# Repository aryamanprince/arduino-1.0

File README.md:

Files to be submitted for Zine robotics and research group interview

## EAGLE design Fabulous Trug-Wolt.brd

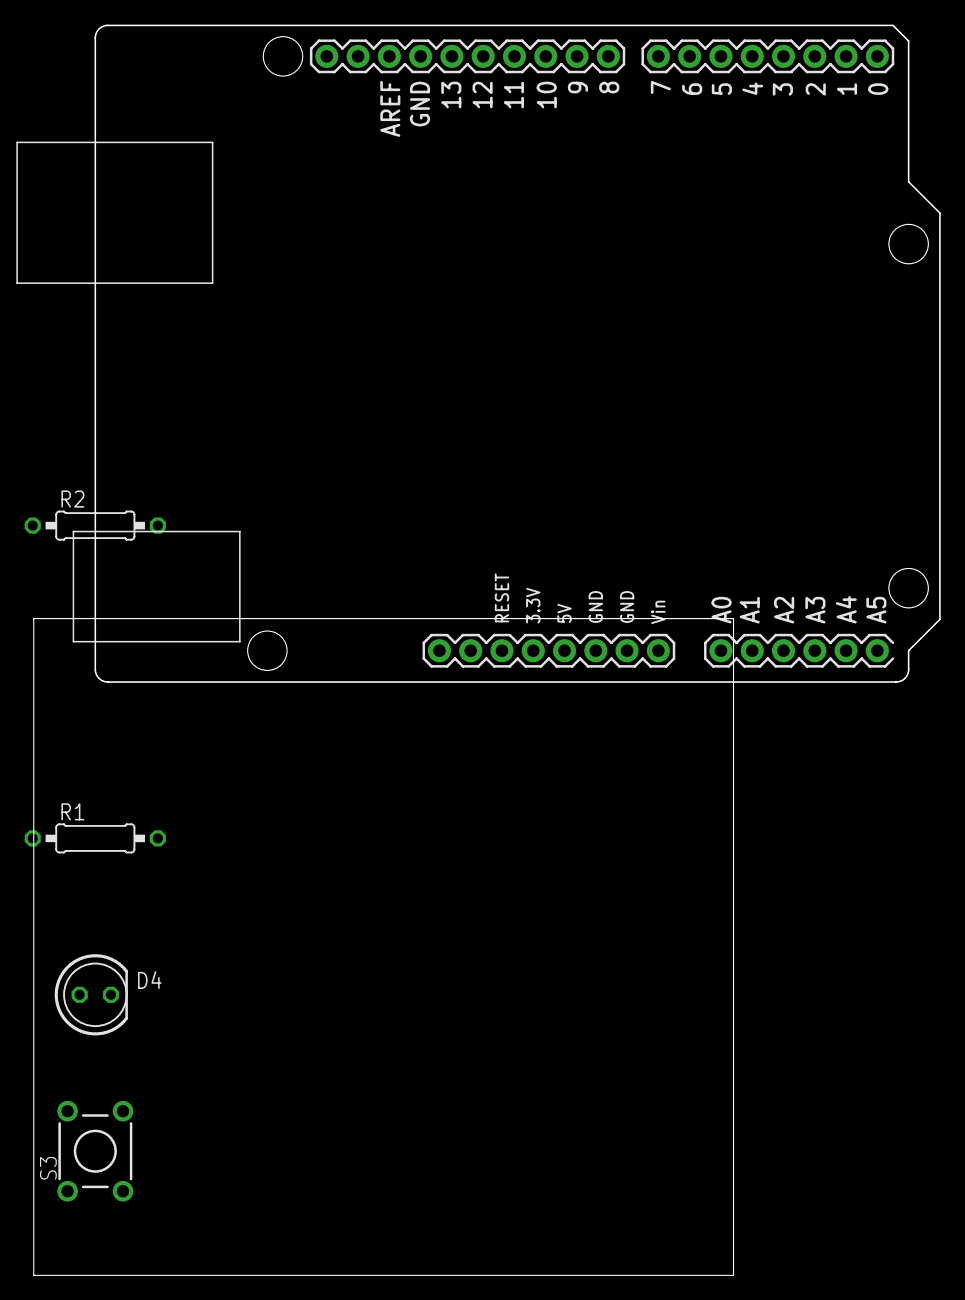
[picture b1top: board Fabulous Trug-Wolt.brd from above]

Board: 2 copper layers, 73.5 x 101.4 mm, 5 parts (0 on the bottom side), 5 nets, no tracks yet.

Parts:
D4: LED5MM
R1, R2: 1k‎Ω; 0207/10
S3: TL1105
U2: ARDUINO_UNO

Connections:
unnamed: D4.K, R1.2
unnamed: D4.A, U2.12
unnamed: S3.4, U2.5V
unnamed: R2.2, S3.3, U2.5
unnamed: R1.1, R2.1, U2.GND
